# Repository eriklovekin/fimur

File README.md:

# Fused Inertial Measurement Unit aRray (FIMUR)
Can the performance of high-cost IMUs be matched through the fusion of a large array of MEMS IMUs?

## Build
`cargo build` will fail when run from the root of the repo because there are two compilation targets
This project uses a [justfile](https://just.systems/man/en/) to automate build commands.
- To build all firmware crates (targetting ESP32), run `just build`
- To build the fusion-py crate, run `just pybuild`
- To build everything, run `just all`
- To clean all build artifacts, run `just clean`

## Deploy
To deploy to the ESP32 target, run `just run`

## Hardware
This project targets an [ESP32-C6-DevKitC-1](https://docs.espressif.com/projects/esp-dev-kits/en/latest/esp32c6/esp32-c6-devkitc-1/user_guide.html), connected via the onboard USB-C ports. For best performance, connect to the ESP32-C6 native USB port (The left port looking at the board from the top with the USB ports pointing up).

## Coordinate Frames
### Sensor (S)
The S frame is the frame in which the sensor outputs measurements.

### Filter (F)
The F frame is the frame in which the output of the filter is represented. The origin and orientation of each IMU must be initialized in this frame. 
    Origin: position of the S origin of the IMU as (x_F, y_F, z_F)
    Rotation: Direction cosine matrix from IMU S frame to F frame

### Wake (W)
The W frame is an inertial frame colocated with the F frame at filter startup (wake). It does not move with the sensor, and is the frame in which position estimates are represented.

### ENU (L)
The ENU frame is an inertial frame with origin colocated with the Filter frame origin.

## Filters

### 1: Choi-Dinkel
The fusion-core crate implements the algorithm described in [Ref 8](https://hollydinkel.github.io/assets/pdf/AAS2025.pdf) with some modifications. The filter is essentially an equally weighted average of measurements from all IMUs rotated into the virtual (Filter) frame. There is some fancy math that projects out the $\alpha\times r$ acceleration term by multiplying by its nullspace.

The filter assumes:
- IMUs rigidly connected to eachother
- *i*th accelerometer and gyroscope are colocated
- IMU relative poses known apriori
    - Different from the referenced algorithm which estimates relative poses as part of an initial extrinsic calibration step

This filter is implemented in the fusion-core crate and is accessible for use both in the online Rust environment and an offline python environment via an interface defined in the fusion-py crate (see [offline_fusion.py](./offline_fusion.py)). 
Note: for use in either environment, `N_IMUS` as defined in fusion-core must agree with the number of IMUs the algorithm is being run on.

## Configuration
IMU configurations are defined individually in TOML files in the `sensor-config/` directory. These are parsed by both the online (TODO) and offline fusion processes. The configs include:
- Adressing
- Sensor settings
- Pose
manifest.toml defines which imus are used in the build and the size of the list sets the value of N_IMUS, used both online and offline.

The config files are ingested at build time in the fusion-core build.rs. Structs that are ultimately generated from these configs are defined in the fusion-core config module. 
The configs are ingested at build time to allow the use of an std toml parser which makes everything easier. This autogenerates a rust source file that explicitly defines the sensor structs from the configs and is then included in the fusion-core config module.
The current implementation assumes a single multiplexer is in use and explicitly instantiates each of the buses on that multiplexer. Future work will allow an arbitrary set of multiplexers/buses to be used, but is too much of a rabit hole for now...

## Dependencies

### Python
Running with python 3.12.3
Ensure the following libraries are installed using `pip install <library>`
- serial
- pyserial
- pandas
- numpy
- pyqtgraph
- pyside6
- allantools
- PyQt5
- tqdm

### PyQt
- `sudo apt update`
- `sudo apt install libxcb-cursor0`

### Just
-  `sudo apt install just`

## References
1 [Interactive Kalman Filter Tutorial](https://arthurlovekin.com/interactive-kalman-filter/index.html)

2 [Extended Kalman Filter](https://mwrona.com/posts/attitude-ekf/)

3 Sarabandi, S; Thomas, F - Accurate Computation of Quaternions from Rotation Matrices

4 [Rotation Quaternions, and How to Use Them](https://danceswithcode.net/engineeringnotes/quaternions/quaternions.html)

5 [AHRS Complimenatary Filter](https://ahrs.readthedocs.io/en/latest/filters/complementary.html)

6 [Building a Virtual Gyro](https://www.nxp.com/company/about-nxp/smarter-world-blog/BL-BUILDING-VIRTUAL-GYRO)

7 [Gauss Markov Theorem](https://www.statlect.com/fundamentals-of-statistics/Gauss-Markov-theorem)

8 [Sensor Fusion for Distributed Inertial Measurement Units](https://hollydinkel.github.io/assets/pdf/AAS2025.pdf)

9 [Understanding ARW: The Hidden Limit to IMU Accuracy (Part 1)](https://guidenav.com/blog/understanding-arw-the-hidden-limit-to-imu-accuracy-part-1/)

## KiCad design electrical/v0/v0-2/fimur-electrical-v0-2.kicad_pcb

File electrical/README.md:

# FIMUR Electrical
## Naming Convention
Each board has a 3-digit version number: A.B.C
A - major version number
B - board type. 
    1 is ICM20948 i2c breakout;
    2 is i2c multiplexer breakout and esp32 interface
C - minor version number

## IMC20948 Breakout (x.1.x)
I2C Breakout for two ICM20948 9-axis IMUs.
U2 (sensor on the left when text is upright) has I2C address 0x68. U3 has address 0x69.

### Exposes
- I2C bus
    two connectors to allow daisychaining
- pullup pins
    One and only one device on the bus must jump the pullup pins to allow for correct logic operation.
- FSYNC pins
    Future Work: should be able to daisychain all IMUs on this line to synchronize sample times

### v0.1.1
Works. 
- should add some capacitors to the 1.8V power supply as per spec sheet
- print IMU addresses next to them for easy ID

## Multiplexer Interface (x.2.x)
Connects ESP32 with TCA9548A I2C multiplexer.

### Exposes
- i2c bus upstream of multiplexer
    two connectors to allow daisychaining
- pullup pins for upstream i2c bus
    One and only one device on the upstream bus must jump the pullup pins to allow for correct logic operation.
- address pins for multiplexer
    each multiplexer on the upstream i2c bus must have a unique address. Addresses range from 0x70 to 0x77. The default address w/o any address pins driven is 0x70.
- eight multiplexed i2c channels downstream of the multiplexer. 
    These act as their own bus, so devices with the same address can be used if on different channels.

The board uses 3.3V I2C logic supplied directly from the ESP32.

### 0.2.1
Bad: made ESP32 get very hot. Do not use.

### 0.2.2
Fixed issues with 0.2.1. Tested with two IMUs connected to the same and differet channels.

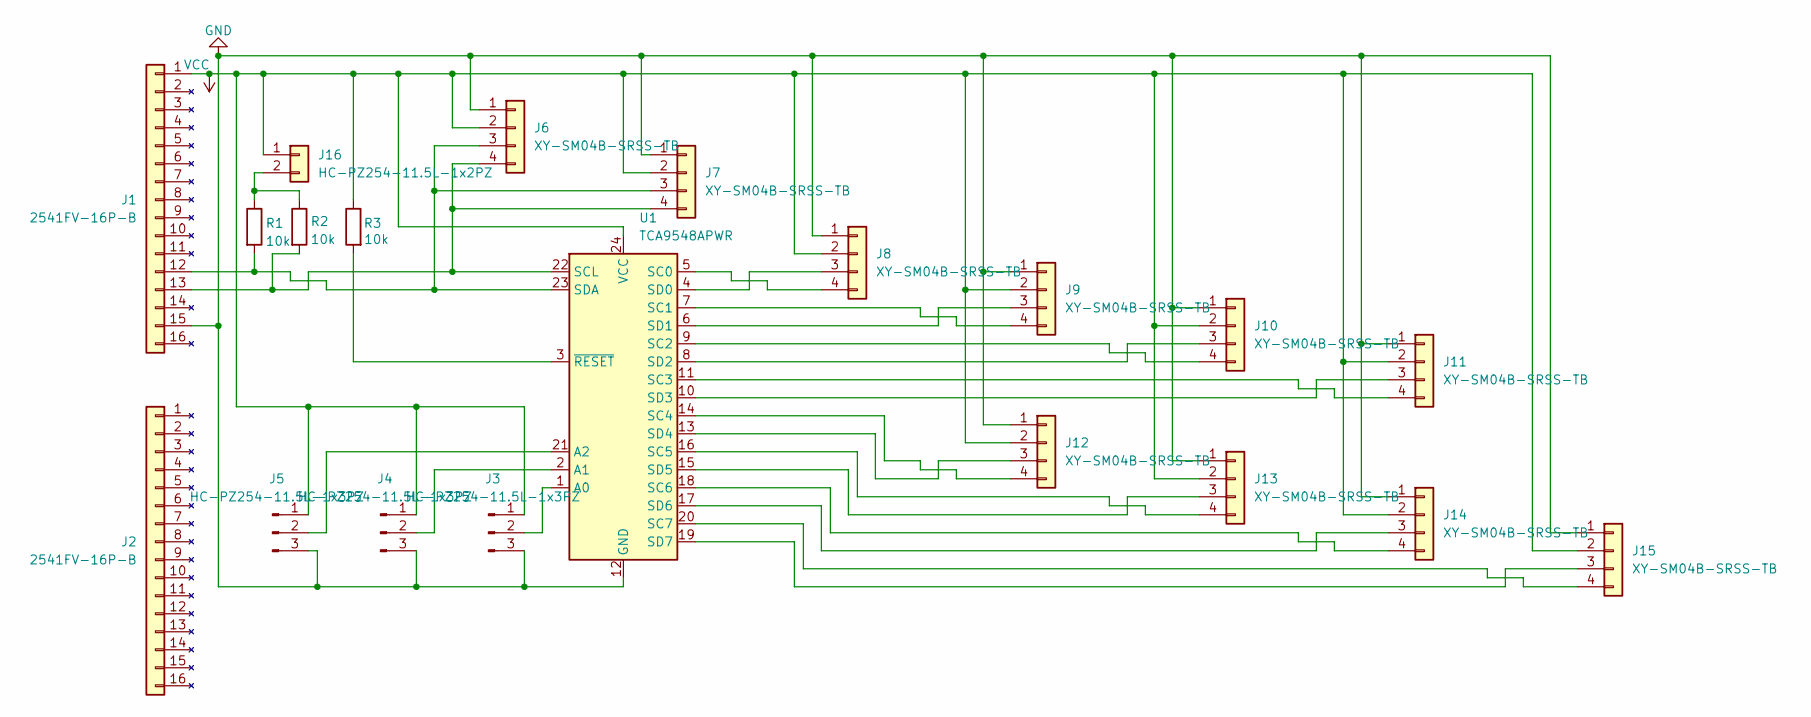
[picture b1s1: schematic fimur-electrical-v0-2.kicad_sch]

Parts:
J1, J2: 2541FV-16P-B; PinSocket_1x16_P2.54mm_Vertical
J3, J4, J5: HC-PZ254-11.5L-1x3PZ; PinHeader_1x03_P2.54mm_Vertical
J6, J7, J8, J9, J10, J11, J12, J13, J14, J15: XY-SM04B-SRSS-TB; JST_SH_SM04B-SRSS-TB_1x04-1MP_P1.00mm_Horizontal
J16: HC-PZ254-11.5L-1x2PZ; PinHeader_1x02_P2.54mm_Vertical
R1, R2, R3: 10k; R_1206_3216Metric
U1: TCA9548APWR; TSSOP-24_4.4x7.8mm_P0.65mm

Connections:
GND: J1.15 (G), J3.3, J4.3, J5.3, J6.1, J7.1, J8.1, J9.1, J10.1, J11.1, J12.1, J13.1, J14.1, J15.1, U1.12 (GND); also elsewhere on the board
unnamed: J1.12 (2), J6.3, J7.3, R1.2, U1.23 (SDA)
unnamed: J1.13 (3), J6.4, J7.4, R2.2, U1.22 (SCL)
unnamed: J3.2, U1.1 (A0)
unnamed: J4.2, U1.2 (A1)
unnamed: J5.2, U1.21 (A2)
unnamed: J8.3, U1.4 (SD0)
unnamed: J8.4, U1.5 (SC0)
unnamed: J9.3, U1.6 (SD1)
unnamed: J9.4, U1.7 (SC1)
unnamed: J10.3, U1.8 (SD2)
unnamed: J10.4, U1.9 (SC2)
unnamed: J11.3, U1.10 (SD3)
unnamed: J11.4, U1.11 (SC3)
unnamed: J12.3, U1.13 (SD4)
unnamed: J12.4, U1.14 (SC4)
unnamed: J13.3, U1.15 (SD5)
unnamed: J13.4, U1.16 (SC5)
unnamed: J14.3, U1.17 (SD6)
unnamed: J14.4, U1.18 (SC6)
unnamed: J15.3, U1.19 (SD7)
unnamed: J15.4, U1.20 (SC7)
unnamed: J16.2, R1.1, R2.1
unnamed: R3.2, U1.3 (~RESET)
VCC: J1.1 (3V3), J3.1, J4.1, J5.1, J6.2, J7.2, J8.2, J9.2, J10.2, J11.2, J12.2, J13.2, J14.2, J15.2, J16.1, R3.1, U1.24 (VCC); also elsewhere on the board

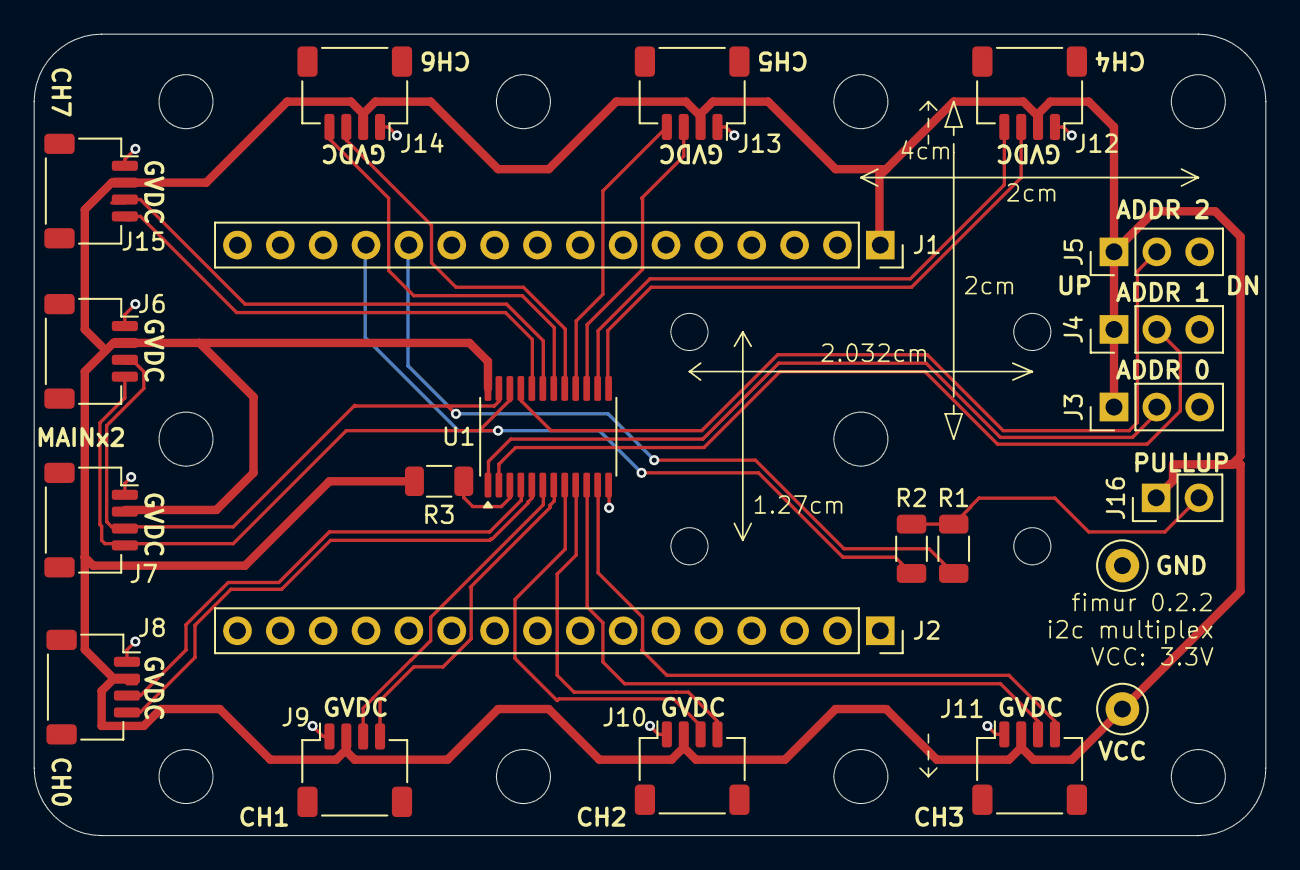
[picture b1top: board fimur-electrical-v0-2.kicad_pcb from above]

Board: 2 copper layers, 73.0 x 47.5 mm, 22 parts (0 on the bottom side), 25 nets.

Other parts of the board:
GND: TestPoint_Loop_D1.80mm_Drill1.0mm_Beaded
VCC: TestPoint_Loop_D1.80mm_Drill1.0mm_Beaded

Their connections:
GND: GND.1; also elsewhere on the board
VCC: VCC.1; also elsewhere on the board

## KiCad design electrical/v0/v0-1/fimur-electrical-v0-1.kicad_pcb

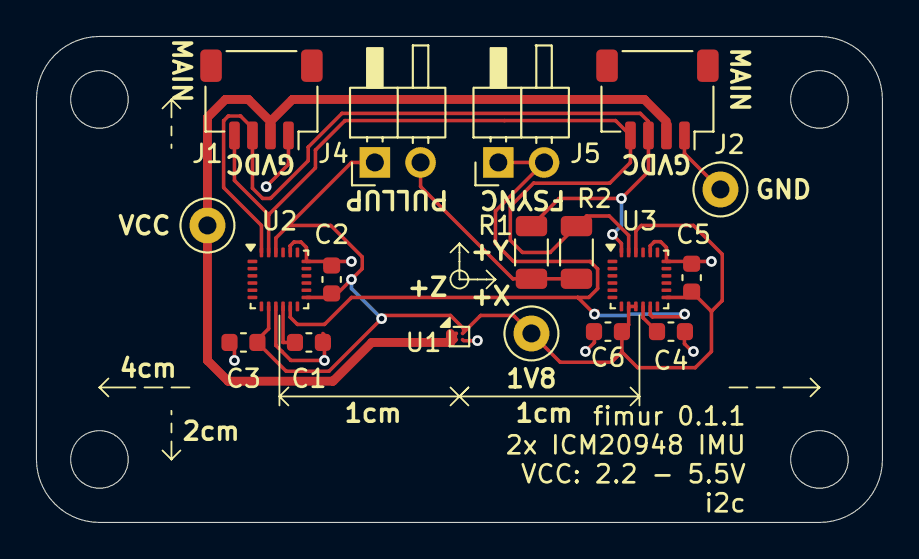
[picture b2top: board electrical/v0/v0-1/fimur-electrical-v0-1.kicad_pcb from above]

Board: 2 copper layers, 47.0 x 27.0 mm, 18 parts (0 on the bottom side), 9 nets.

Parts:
1V8: TestPoint_Loop_D1.80mm_Drill1.0mm_Beaded
C1, C2, C3, C4, C5, C6: 0.1 uF; C_0603_1608Metric
GND: TestPoint_Loop_D1.80mm_Drill1.0mm_Beaded
J1, J2: Conn_01x04_Pin; JST_SH_SM04B-SRSS-TB_1x04-1MP_P1.00mm_Horizontal
J4, J5: Conn_01x02; PinHeader_1x02_P2.54mm_Horizontal
R1, R2: 10k; R_1206_3216Metric
U1: NCP163AFCS180T2G; WLCSP-4_0.64x0.64mm_Layout2x2_P0.35mm
U2, U3: ICM-20948; InvenSense_QFN-24_3x3mm_P0.4mm
VCC: TestPoint_Loop_D1.80mm_Drill1.0mm_Beaded

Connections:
GND: C1.2, C2.2, C3.2, C4.2, C5.2, C6.2, GND.1, J1.1, J2.1, U1.B2 (GND), U2.9 (SDO/AD0), U2.18 (GND), U2.20 (GND), U3.18 (GND), U3.20 (GND)
unnamed: J1.2, J2.2, U1.A1 (VIN), U1.B1 (EN), VCC.1
unnamed: J1.3, J2.3, R1.2, U2.24 (SDA/SDI), U3.24 (SDA/SDI)
unnamed: J1.4, J2.4, R2.2, U2.23 (SCL/SCLK), U3.23 (SCL/SCLK)
unnamed: 1V8.1, C2.1, C3.1, C5.1, C6.1, J4.1, U1.A2 (VOUT), U2.8 (VDDIO), U2.13 (VDD), U2.22 (~CS), U3.8 (VDDIO), U3.9 (SDO/AD0), U3.13 (VDD), U3.22 (~CS)
unnamed: J4.2, R1.1, R2.1
unnamed: J5.1, J5.2, U2.11 (FSYNC), U3.11 (FSYNC)
unnamed: C1.1, U2.10 (REGOUT)
unnamed: C4.1, U3.10 (REGOUT)

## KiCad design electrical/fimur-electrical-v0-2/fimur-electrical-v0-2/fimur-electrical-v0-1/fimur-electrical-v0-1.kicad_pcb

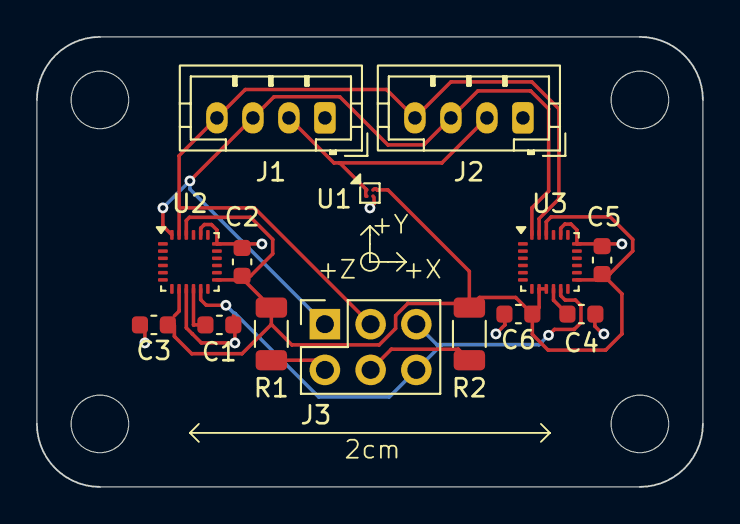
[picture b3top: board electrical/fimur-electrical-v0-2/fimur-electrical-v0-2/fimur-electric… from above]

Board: 2 copper layers, 37.0 x 25.0 mm, 14 parts (0 on the bottom side), 10 nets.

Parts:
C1, C2, C3, C4, C5, C6: 0.1 uF; C_0603_1608Metric
J1, J2: Conn_01x04_Pin; JST_PH_B4B-PH-K_1x04_P2.00mm_Vertical
J3: Conn_02x03_Odd_Even; PinSocket_2x03_P2.54mm_Vertical
R1, R2: 10k; R_1206_3216Metric
U1: NCP163AFCS180T2G; WLCSP-4_0.64x0.64mm_Layout2x2_P0.35mm
U2, U3: ICM-20948; InvenSense_QFN-24_3x3mm_P0.4mm

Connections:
GND: C1.2, C2.2, C3.2, C4.2, C5.2, C6.2, J1.1, J2.1, U1.B2 (GND), U2.9 (SDO/AD0), U2.18 (GND), U2.20 (GND), U3.18 (GND), U3.20 (GND)
unnamed: J1.2, J2.2, U1.A1 (VIN), U1.B1 (EN)
unnamed: J1.3, J2.3, J3.1, U2.24 (SDA/SDI), U3.24 (SDA/SDI)
unnamed: J1.4, J2.4, J3.3, U2.23 (SCL/SCLK), U3.23 (SCL/SCLK)
unnamed: J3.2, R1.2
unnamed: J3.4, R2.2
unnamed: J3.5, J3.6, U2.11 (FSYNC), U3.11 (FSYNC)
unnamed: C2.1, C3.1, C5.1, C6.1, R1.1, R2.1, U1.A2 (VOUT), U2.8 (VDDIO), U2.13 (VDD), U2.22 (~CS), U3.8 (VDDIO), U3.9 (SDO/AD0), U3.13 (VDD), U3.22 (~CS)
unnamed: C1.1, U2.10 (REGOUT)
unnamed: C4.1, U3.10 (REGOUT)

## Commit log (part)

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2025-12-24 initial commit; Hello World from esp
2025-12-25 rgb blinky running
2025-12-28 reading raw values from encoder
2025-12-28 reading encoder angles in degrees
2025-12-28 cleanup encoder reading
2026-02-09 reorganization into crates
2026-02-12 icm-traits creates; bank0 registers defined for icm20948
2026-02-18 added all register banks to icm driver
2026-02-18 imu-traits and icm crates added to workspace Cargo.toml and Cargo.lock
2026-02-18 icm implementations of imu-traits
2026-02-18 added icm and imu-traits crates to firmware dependencies
2026-02-20 reading imu telemetry!
2026-02-20 live qt plots of accel and gyro data
2026-02-20 auto-find port connected to esp32
2026-02-21 estimate attitude by integrating raw gyroscope data
2026-02-21 functions to read accel in mps2 and G; functions to read gyro in dps and rps
2026-02-22 estimating velocity and attitude by direct integration; working poorly; added velocity and position plots
2026-02-25 accel and gyro scale setters and getters implemented and build:
2026-02-27 select_register_bank allows set_xxx_scale to work
2026-02-27 get_bank method returns register bank in which register exists
2026-02-27 added bank select to set_accelerometer_scale
2026-02-27 added select_register_bank to sensor reading functions
2026-02-27 concisified accel data getters and setters
2026-03-02 2-imu pcb schematic and layout
2026-03-03 i2c multiplexer board schematic
2026-03-05 multiplex schematic and layout and standardization with 2-imu board
2026-03-07 cleanup of v10.1.1
2026-03-11 all kicad files for v0 boards
2026-03-11 major cleanup of kicad fluff
2026-03-13 initializing two imus on same i2c bus
2026-03-13 printing data from both imus
2026-03-13 plotting data from two imus
2026-03-17 added origin and rotation fields to icm20948 struct
2026-03-26 v2 of multiplex board
2026-03-26 sensor mount members and utility functions
2026-04-01 functions to convert between DCM and quaternions
2026-04-01 typo fix
2026-04-01 added references to README
2026-04-18 added measurement struct to icm20948 struct
2026-04-21 store DCM insteadof quaternion; start of Filter struct
2026-04-21 generic average filters
2026-05-02 basic complimentary filter for attitude
2026-05-20 lots of syntax fixes to get it building again
2026-05-28 started integrating Filter into main; does not build
2026-05-29 builds again
2026-05-29 cleanup many compile warnings and use filter report_raw
2026-06-09 added intuitive filter flow diagram
2026-06-09 reports of current estimated state
2026-06-27 state transition as part of Kalman filter
